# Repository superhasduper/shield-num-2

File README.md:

# shield-num-2
it is an other Arduino shield pcb made in kicad

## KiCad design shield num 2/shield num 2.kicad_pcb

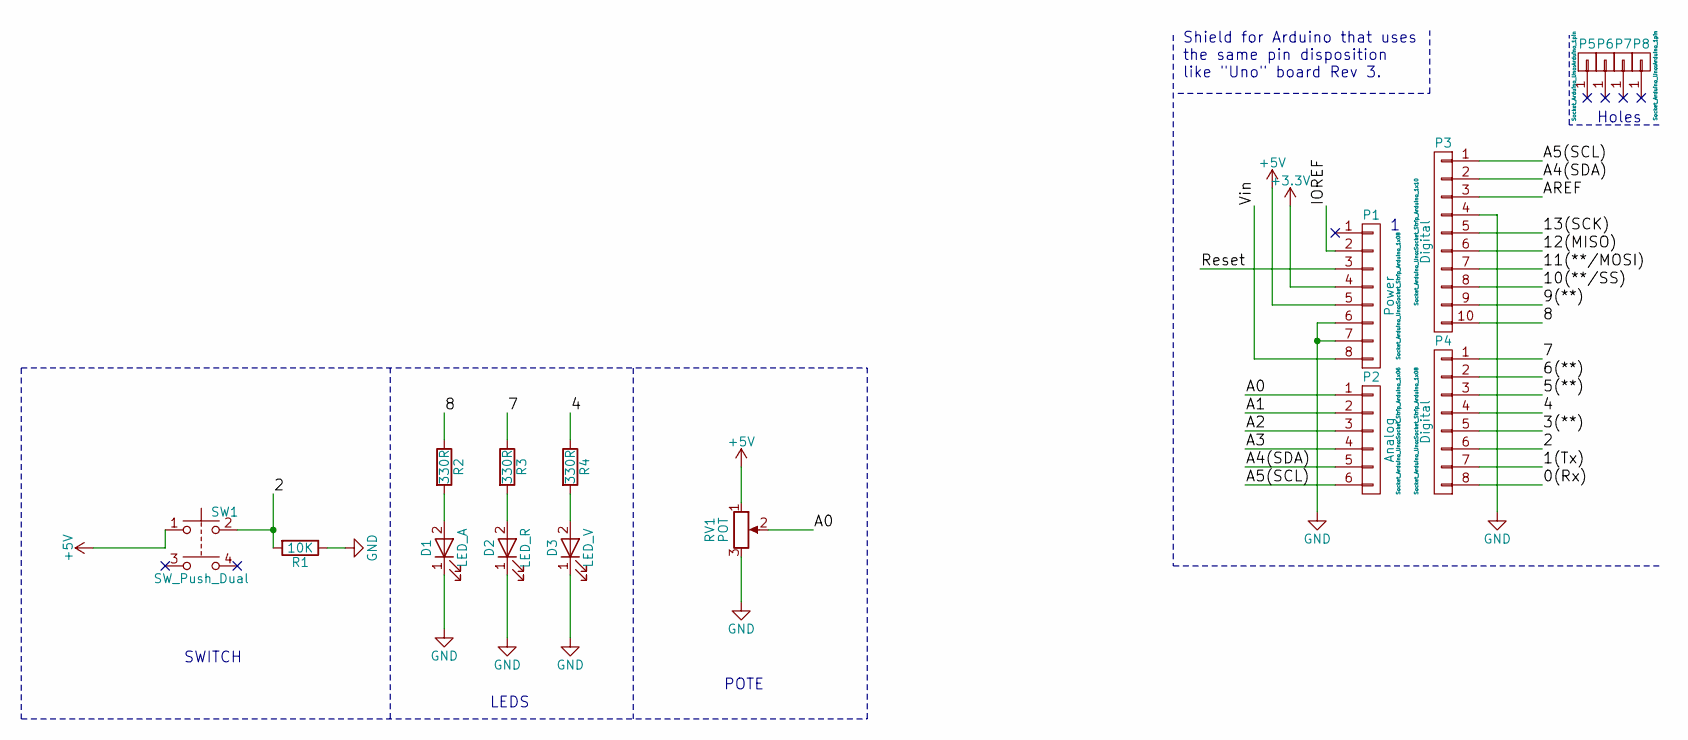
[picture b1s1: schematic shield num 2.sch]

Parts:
D1: LED_A; LED_D5.0mm
D2: LED_R; LED_D5.0mm
D3: LED_V; LED_D5.0mm
P1: Power; Socket_Strip_Arduino_1x08
P2: Analog; Socket_Strip_Arduino_1x06
P3: Digital; Socket_Strip_Arduino_1x10
P4: Digital; Socket_Strip_Arduino_1x08
P5, P6, P7, P8: CONN_01X01; Arduino_1pin
R1: 10K; R_Axial_DIN0207_L6.3mm_D2.5mm_P7.62mm_Horizontal
R2, R3, R4: 330R; R_Axial_DIN0207_L6.3mm_D2.5mm_P7.62mm_Horizontal
RV1: POT; Potentiometer_Trimmer_Piher_PT-10v10_Horizontal_Px10.0mm_Py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
SW1: SW_Push_Dual; SW_PUSH_6mm

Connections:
+3V3: P1.4
+5V: P1.5, RV1.1, SW1.1
/0(Rx): P4.8
/1(Tx): P4.7
/2: P4.6, R1.2, SW1.2
/3(**): P4.5
/4: P4.4, R4.1
/5(**): P4.3
/6(**): P4.2
/7: P4.1, R3.1
/8: P3.10, R2.1
/9(**): P3.9
/10(**/SS): P3.8
/11(**/MOSI): P3.7
/12(MISO): P3.6
/13(SCK): P3.5
/A0: P2.1, RV1.2
/A1: P2.2
/A2: P2.3
/A3: P2.4
/A4(SDA): P2.5, P3.2
/A5(SCL): P2.6, P3.1
/AREF: P3.3
/IOREF: P1.2
/Reset: P1.3
/Vin: P1.8
GND: D1.1 (K), D2.1 (K), D3.1 (K), P1.6, P1.7, P3.4, R1.1, RV1.3
unnamed: D1.2 (A), R2.2
unnamed: D2.2 (A), R3.2
unnamed: D3.2 (A), R4.2

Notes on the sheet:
Holes
Shield for Arduino that uses the same pin disposition like "Uno" board Rev 3.
LEDS
POTE
SWITCH

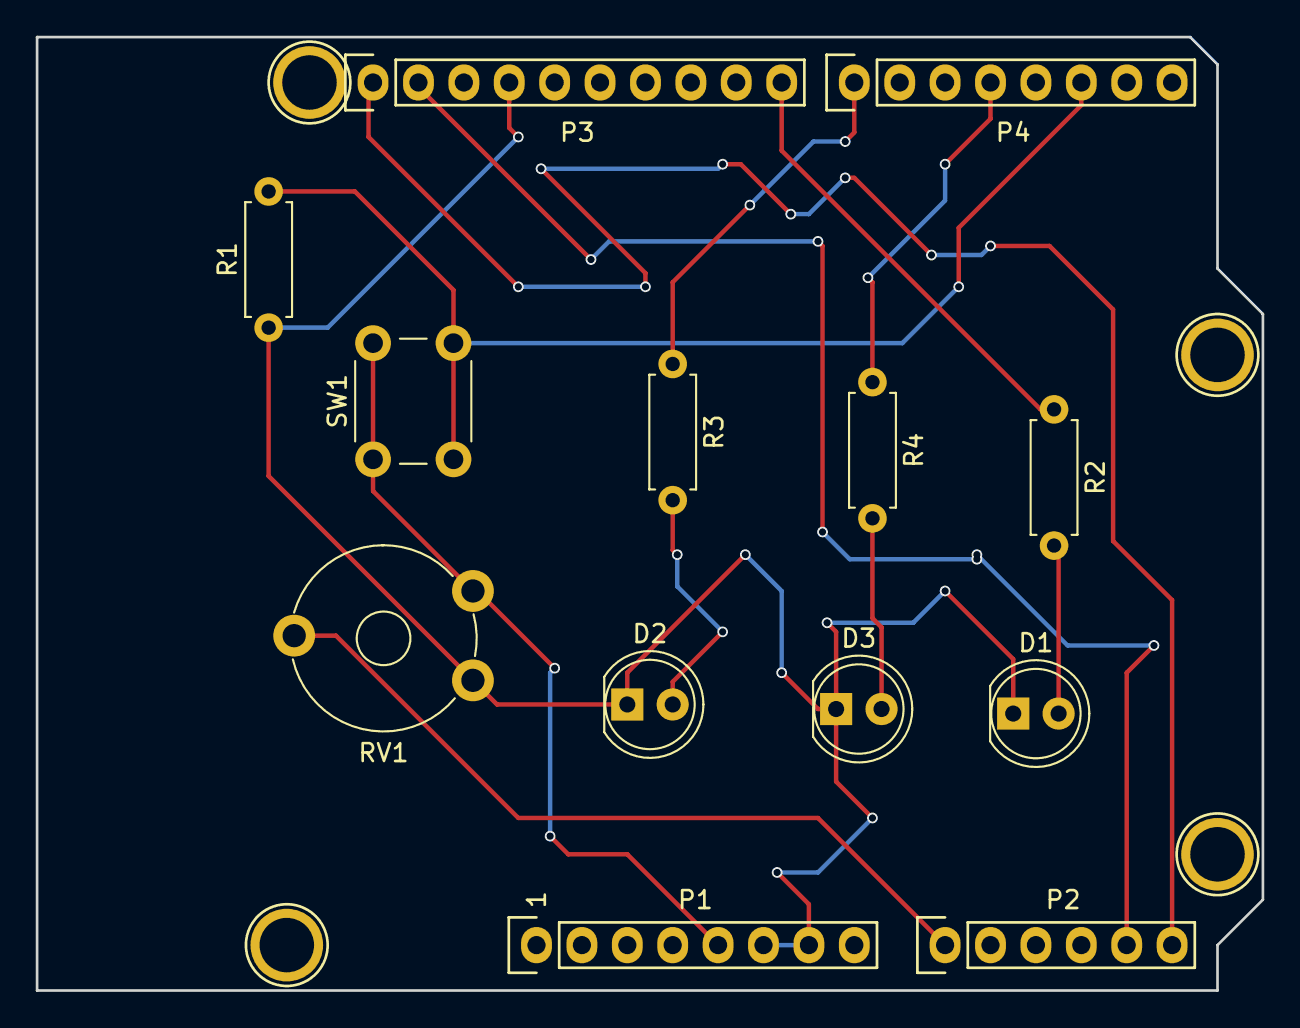
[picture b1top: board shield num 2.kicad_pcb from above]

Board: 2 copper layers, 68.6 x 53.3 mm, 17 parts (0 on the bottom side), 12 nets.

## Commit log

2019-07-07 here is everything
